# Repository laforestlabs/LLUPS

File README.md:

# LLUPS — Lithium Li-ion Universal Power Supply

> **Status: Draft / Untested** — Schematic and layout are procedurally generated and have not been fabricated or validated on hardware. Review all design choices and run DRC before ordering boards.

A compact PCB module providing regulated 5V and 3.3V power from two 18650 Li-ion cells (1S2P), charged via USB-C with passthrough capability.

## Specs

| Parameter | Value |
|---|---|
| Cells | 2x 18650 in parallel (1S2P), 3.7V nominal |
| Input | USB-C 5V (default power, no PD) |
| Outputs | 5V @ 1A (boost), 3.3V @ 500mA (LDO), raw VBAT |
| Charger | BQ24072, 1-2A CC/CV with power path |
| Protection | HY2113 (2.8V hard cutoff) + LN61C supervisor (3.3V operating cutoff) |
| Boost | MT3608, 5V from 3.3-4.2V input |
| LDO | AP2112K-3.3, 600mA |
| Board | 90×58mm default (variable with `--board-size-search`), 2-layer, 1oz Cu |

## Getting Started

```bash
# Clone with submodules
git clone --recurse-submodules https://github.com/laforestlabs/LLUPS.git
cd LLUPS

# If already cloned without submodules
git submodule update --init --recursive

# Install KiCraft tooling (required for all CLI commands)
pip install -e KiCraft/

# Or with GUI support
pip install -e "KiCraft/[gui]"
```

**Requirements:**
- Python 3.10+
- [KiCad 9](https://www.kicad.org/) with pcbnew Python bindings
- [FreeRouting](https://github.com/freerouting/freerouting) JAR (for automated routing)
- [KiCraft](https://github.com/laforestlabs/KiCraft) submodule (included, installed via pip above)

## Core Files

```text
LLUPS.kicad_pro          # KiCad 9 project
LLUPS.kicad_sch          # Schematic
LLUPS.kicad_pcb          # PCB layout
generate_project.py      # Regenerates project artifacts
spec.md                  # Design specification
BOM.csv / BOM.xlsx       # Bill of materials
KiCraft/                 # KiCraft tooling (git submodule) — https://github.com/laforestlabs/KiCraft
```

## Regenerating

```bash
python3 generate_project.py
```

Requires KiCad 9 CLI tools (`kicad-cli`) for netlist export.

## Running the Optimizer

```bash
autoexperiment LLUPS.kicad_pcb --rounds 100
```

The optimizer iterates placement and routing, keeping candidates that improve the overall score and discarding the rest. The best layout is saved to `LLUPS_best.kicad_pcb`.

### Search Space Flags

| Flag | Effect |
|---|---|
| `--unlock-all` | Unlock all footprints (batteries, connectors, mounting holes) — edge scoring still incentivizes edge placement |
| `--board-size-search` | Add board width (60–120mm) and height (40–80mm) to the parameter search space (5mm steps) |

```bash
# Full exploration: unlock all footprints + vary board size over 150 rounds
autoexperiment LLUPS.kicad_pcb \
  --rounds 150 --unlock-all --board-size-search
```

## Experiment Manager GUI

A standalone NiceGUI web app for configuring, running, monitoring, and analyzing experiments.

```bash
# Install KiCraft with GUI dependencies (first time only)
pip install -e "KiCraft/[gui]"

# Launch the GUI
python3 -m kicraft.gui
# then open http://localhost:8080
```

### GUI Tabs

| Tab | Purpose |
|---|---|
| **Setup** | Configure search dimensions, mutation strategy, score weights, feature toggles (unlock all, board size search), mutation search bounds (min/max per parameter), and save/load presets |
| **Monitor** | Start/stop experiments, live score chart, status cards, round-by-round progress |
| **Analysis** | Browse past experiments, score trend plots, parameter sensitivity (Spearman), correlation matrix, convergence analysis, CSV export |
| **Board** | PCB layout viewer with layer selection and component list |

Experiment data is stored in `.experiments/llups.db` (SQLite). Existing JSONL logs are auto-imported on first launch.

## Monitoring Your Run

> All monitoring is read-only — it reads output files and never interferes with the experiment. Zero performance impact.

**During a run** — pick any of these (in a second terminal):

```bash
# Experiment Manager GUI (recommended — includes live charts + analysis)
python3 -m kicraft.gui

# Or: one-line terminal status
watch -n2 cat .experiments/run_status.txt

# Or: leave the HTML report open; it rebuilds after each round and refreshes itself
xdg-open report.html
```

**After a run:**

```bash
# Animated layout evolution
xdg-open .experiments/progress.gif

# Score dashboard (PNG)
xdg-open .experiments/experiments_dashboard.png

# Interactive HTML report (richest view; rebuilt live during the run and finalized at the end)
generate-report .experiments/ -o report.html
xdg-open report.html
```

For monitoring during a run, the KiCraft GUI (`python -m kicraft.gui`) is the primary tool — it shows live per-leaf round progress, score plots, render thumbnails, and per-component pin controls. The CLI artifacts above (`run_status.txt`, `progress.gif`, `experiments_dashboard.png`, `report.html`) are still produced for headless workflows.

## Architecture & Scoring

- [`docs/architecture.md`](docs/architecture.md) — system diagrams and layer responsibilities
- [`docs/footprint-layout.md`](docs/footprint-layout.md) — placement engine details
- [`docs/auto-trace.md`](docs/auto-trace.md) — routing engine details
- [`docs/scoring.md`](docs/scoring.md) — scoring formulas and weight breakdowns

Static QA score (independent of the optimizer):

```bash
score-layout LLUPS.kicad_pcb
```

## KiCraft CLI Commands

Automation commands using the KiCad 9 `pcbnew` Python API, provided by the [KiCraft](https://github.com/laforestlabs/KiCraft) submodule:

| Command | Purpose |
|---|---|
| `list-footprints` | List components with positions |
| `check-trace-widths` | Find traces below minimum width |
| `run-drc` | Report DRC markers |
| `net-report` | List nets and pad counts |
| `move-component` | Move a footprint to X,Y |
| `arrange-grid` | Arrange components in a grid |
| `align-components` | Align components along an axis |

All available as CLI commands after `pip install -e KiCraft/`.

## Subcircuits Workflow

The hierarchical/subcircuits redesign is currently focused on a real leaf-first routing flow:

1. parse the true schematic hierarchy from `LLUPS.kicad_sch`
2. extract each leaf sheet into a local board state
3. stamp a real KiCad leaf board under `.experiments/subcircuits/<slug>/`
4. validate the stamped pre-route leaf board before routing
5. route the leaf through the real FreeRouting path
6. validate the routed leaf artifact before accepting it
7. persist accepted routed copper canonically in `solved_layout.json`

Current verification command:

```bash
solve-subcircuits LLUPS.kicad_sch \
  --pcb LLUPS.kicad_pcb \
  --rounds 1 \
  --route
```

### Leaf render diagnostics

Each leaf artifact may now include a small visual diagnostic bundle under:

```text
.experiments/subcircuits/<slug>/renders/
```

These diagnostics are intended for debugging real stamped/routed leaf boards, not for demo polish. The preferred artifact set is:

- `pre_route_copper_both.png`
- `pre_route_front_all.png`
- `pre_route_drc.json`
- `pre_route_drc_overlay.png` when coordinate-bearing violations exist
- `routed_copper_both.png`
- `routed_front_all.png`
- `routed_drc.json`
- `routed_drc_overlay.png` when coordinate-bearing violations exist
- `pre_vs_routed_contact_sheet.png`

This makes it easier to answer:

- is the stamped pre-route leaf board already illegal?
- are footprints or edge-coupled connectors misaligned to `Edge.Cuts`?
- did FreeRouting add meaningful copper?
- did routing improve or worsen the board visually?

### Current status

The subcircuit pipeline is functional: all 6 LLUPS leaves solve, route, and pass acceptance gates. Parent composition assembles the leaves and routes interconnects via FreeRouting. The pipeline runs to completion without Python exceptions and produces human-inspectable output. The parent acceptance gate currently rejects due to FreeRouting routing quality (a tuning target, not a functional gap). See `ROADMAP.md` for detailed phase status.

## License

GPLv3 — see [LICENSE](LICENSE).

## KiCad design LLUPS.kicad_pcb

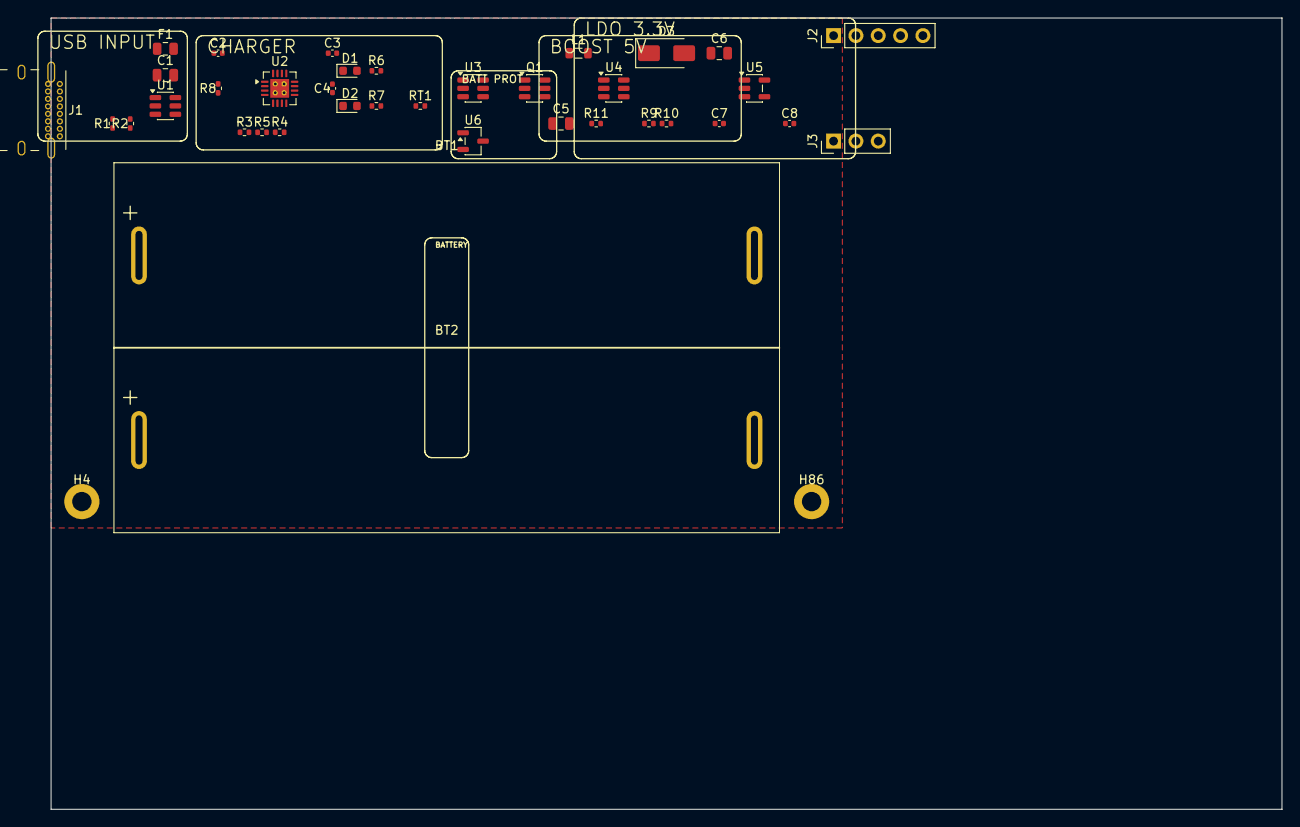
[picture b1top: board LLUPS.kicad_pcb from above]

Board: 2 copper layers, 140.0 x 90.0 mm, 39 parts (0 on the bottom side), 27 nets, no tracks yet.

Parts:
BT1, BT2: 18650; BatteryHolder_MYOUNG_BH-18650-A1AJ006
C1, C5: 10u; C_0805_2012Metric
C2, C3, C4: 4.7u; C_0402_1005Metric
C6: 22u; C_0805_2012Metric
C7, C8: 1u; C_0402_1005Metric
D1: CHG; LED_0603_1608Metric
D2: PGOOD; LED_0603_1608Metric
D3: SS14; D_SMA
F1: 2A_PTC; Fuse_0805_2012Metric
H4, H86: MountingHole; MountingHole_2.2mm
J1: USB_C; USB_C_Receptacle_GCT_USB4085
J2: Output; PinHeader_1x05_P2.54mm_Vertical
J3: Debug; PinHeader_1x03_P2.54mm_Vertical
L1: 4.7u; L_0805_2012Metric
Q1: FS8205A; SOT-23-6
R1, R2: 5.1k; R_0402_1005Metric
R3, R6, R7: 1k; R_0402_1005Metric
R4: 1.5k; R_0402_1005Metric
R5, R8, R10: 10k; R_0402_1005Metric
R9: 75k; R_0402_1005Metric
R11: 100k; R_0402_1005Metric
RT1: 10k_NTC; R_0402_1005Metric
U1: USBLC6-2SC6; SOT-23-6
U2: BQ24072; VQFN-16-1EP_3.5x3.5mm_P0.5mm_EP2.1x2.1mm
U3: HY2113-KB5B; SOT-23-6
U4: MT3608; SOT-23-6
U5: AP2112K-3.3; SOT-23-5
U6: LN61CN3302MR-G; SOT-23-3

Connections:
/3V3: C8.1, J2.2, U5.5
/5V: C6.1, C7.1, D3.1, J2.1, R9.1, U5.1
/CELL_NEG: BT1.2, BT2.2, Q1.4, U3.6
/CHG_N: D1.1, J3.3, U2.9
/EN: J2.4, R11.2, U4.4, U5.3, U6.3
/NTC_SENSE: J3.2, R8.2, RT1.1, U2.1
/VBAT: BT1.1, BT2.1, C4.1, J2.5, J3.1, R8.1, U2.2, U2.3, U3.5, U6.1
/VBUS: C1.1, C2.1, F1.1, U1.5, U2.13
/VSYS: C3.1, R6.2, R7.2, R11.1, U2.5, U2.6, U2.10, U2.11
/VSYS_BOOST: C5.1, L1.2, U4.5
GND: C1.2, C2.2, C3.2, C4.2, C5.2, C6.2, C7.2, C8.2, J1.A1, J1.A12, J1.B1, J1.B12, J1.S1, J2.3, Q1.1, R1.2, R2.2, R3.1, R4.1, R5.1, R10.2, RT1.2, U1.2, U2.8, U2.17, U3.2, U4.2, U5.2, U6.2
unnamed: D1.2, R6.1
unnamed: D2.2, R7.1
unnamed: D2.1, U2.7
unnamed: D3.2, L1.1, U4.1
unnamed: F1.2, J1.A4, J1.A9, J1.B4, J1.B9
unnamed: J1.A5, U1.1
unnamed: J1.B5, U1.3
unnamed: Q1.3, Q1.6
unnamed: Q1.2, U3.1
unnamed: Q1.5, U3.3
unnamed: R1.1, U1.6
unnamed: R2.1, U1.4
unnamed: R4.2, U2.12
unnamed: R3.2, U2.16
unnamed: R5.2, U2.14
unnamed: R9.2, R10.1, U4.3

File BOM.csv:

Designator,Qty,Value,Description,Package,MPN,Manufacturer,LCSC Part,Est. Price @100,LCSC URL
J1,1,USB_C,USB-C Receptacle USB 2.0 16-pin,USB-C Mid-Mount,USB4085-GF-A,GCT,C7095263,$0.50,https://www.lcsc.com/product-detail/C7095263.html
F1,1,2A_PTC,Resettable PTC Fuse 200mA 9V,0805,MF-PSMF020X-2,BOURNS,C89657,$0.03,https://www.lcsc.com/product-detail/C89657.html
U1,1,USBLC6-2SC6,USB ESD Protection Array,SOT-23-6,USBLC6-2SC6,TECH PUBLIC,C2827654,$0.02,https://www.lcsc.com/product-detail/C2827654.html
R1,1,5.1k,CC1 Pull-down Resistor,0402,0402WGF5101TCE,UNI-ROYAL,C25905,$0.001,https://www.lcsc.com/product-detail/C25905.html
R2,1,5.1k,CC2 Pull-down Resistor,0402,0402WGF5101TCE,UNI-ROYAL,C25905,$0.001,https://www.lcsc.com/product-detail/C25905.html
C1,1,10u,VBUS Input Capacitor,0805,CL21A106KAYNNNE,Samsung,C15850,$0.01,https://www.lcsc.com/product-detail/C15850.html
U2,1,BQ24072,Li-Ion Charger with Power Path,VQFN-16,BQ24072RGTR,Texas Instruments,C140288,$0.67,https://www.lcsc.com/product-detail/C140288.html
C2,1,4.7u,Charger IN Capacitor,0402,CL05A475MP5NRNC,Samsung,C23733,$0.003,https://www.lcsc.com/product-detail/C23733.html
C3,1,4.7u,VSYS Capacitor,0402,CL05A475MP5NRNC,Samsung,C23733,$0.003,https://www.lcsc.com/product-detail/C23733.html
C4,1,4.7u,VBAT Capacitor,0402,CL05A475MP5NRNC,Samsung,C23733,$0.003,https://www.lcsc.com/product-detail/C23733.html
R3,1,1k,ISET Resistor,0402,0402WGF1001TCE,UNI-ROYAL,C11702,$0.0004,https://www.lcsc.com/product-detail/C11702.html
R4,1,1.5k,ILIM Resistor,0402,0402WGF1501TCE,UNI-ROYAL,C25867,$0.001,https://www.lcsc.com/product-detail/C25867.html
R5,1,10k,TMR Resistor,0402,RC0402FR-0710KL,YAGEO,C60490,$0.0004,https://www.lcsc.com/product-detail/C60490.html
R6,1,1k,CHG LED Resistor,0402,0402WGF1001TCE,UNI-ROYAL,C11702,$0.0004,https://www.lcsc.com/product-detail/C11702.html
R7,1,1k,PGOOD LED Resistor,0402,0402WGF1001TCE,UNI-ROYAL,C11702,$0.0004,https://www.lcsc.com/product-detail/C11702.html
R8,1,10k,NTC Bias Resistor,0402,RC0402FR-0710KL,YAGEO,C60490,$0.0004,https://www.lcsc.com/product-detail/C60490.html
D1,1,CHG,Charge Status LED (Red),0603,KT-0603R,Hubei KENTO,C2286,$0.003,https://www.lcsc.com/product-detail/C2286.html
D2,1,PGOOD,Power Good LED (Green),0603,LTST-C193TGKT-5A,LITEON,C12065,$0.017,https://www.lcsc.com/product-detail/C12065.html
BT1,1,18650,18650 Battery Holder,Through-Hole,BH-18650-A1AJ006,MYOUNG,C5290175,$0.26,https://www.lcsc.com/product-detail/C5290175.html
BT2,1,18650,18650 Battery Holder,Through-Hole,BH-18650-A1AJ006,MYOUNG,C5290175,$0.26,https://www.lcsc.com/product-detail/C5290175.html
RT1,1,10k_NTC,NTC Thermistor,0402,NCP15XH103F03RC,Murata,C77131,$0.006,https://www.lcsc.com/product-detail/C77131.html
U3,1,HY2113-KB5B,1-Cell Li-Ion Battery Protection IC (2.8V OD / 3.0V rel),SOT-23-6,HY2113-KB5B,HYCON Tech,C168771,$0.059,https://www.lcsc.com/product-detail/C168771.html
U6,1,LN61CN3302MR-G,Voltage Supervisor 3.3V (disables boost at low battery),SOT-23-3,LN61CN3302MR-G,NATLINEAR,C141417,$0.036,https://www.lcsc.com/product-detail/C141417.html
Q1,1,FS8205A,Dual N-MOSFET for Battery Protection,SOT-23-6,FS8205A,TECH PUBLIC,C2830320,$0.03,https://www.lcsc.com/product-detail/C2830320.html
U4,1,MT3608,1.2MHz Step-Up Boost Converter,SOT-23-6,MT3608,XI'AN Aerosemi,C84817,$0.06,https://www.lcsc.com/product-detail/C84817.html
L1,1,4.7u,Boost Inductor (shielded),1008,PNLS252012-4R7M,DMBJ,C2849432,$0.023,https://www.lcsc.com/product-detail/C2849432.html
D3,1,SS14,Schottky Diode 40V 1A,SMA,SS14,MDD,C2480,$0.01,https://www.lcsc.com/product-detail/C2480.html
C5,1,10u,Boost Input Capacitor,0805,CL21A106KAYNNNE,Samsung,C15850,$0.01,https://www.lcsc.com/product-detail/C15850.html
C6,1,22u,Boost Output Capacitor,0805,0805X226M160NT,FH,C129302,$0.015,https://www.lcsc.com/product-detail/C129302.html
R9,1,75k,FB Divider Top,0402,RC0402FR-0775KL,YAGEO,C137935,$0.0006,https://www.lcsc.com/product-detail/C137935.html
R10,1,10k,FB Divider Bottom,0402,RC0402FR-0710KL,YAGEO,C60490,$0.0004,https://www.lcsc.com/product-detail/C60490.html
R11,1,100k,EN Pull-up Resistor,0402,0402WGF1003TCE,UNI-ROYAL,C25741,$0.001,https://www.lcsc.com/product-detail/C25741.html
U5,1,AP2112K-3.3,600mA LDO 3.3V,SOT-23-5,AP2112K-3.3TRG1,Diodes Inc,C51118,$0.06,https://www.lcsc.com/product-detail/C51118.html
C7,1,1u,LDO Input Capacitor,0402,CL05A105KA5NQNC,Samsung,C52923,$0.005,https://www.lcsc.com/product-detail/C52923.html
C8,1,1u,LDO Output Capacitor,0402,CL05A105KA5NQNC,Samsung,C52923,$0.005,https://www.lcsc.com/product-detail/C52923.html
J2,1,Output,5-Pin Output Header (5V/3.3V/GND/EN/VBAT),2.54mm 1x05,MTP125-1105S1,MINTRON,C358687,$0.03,https://www.lcsc.com/product-detail/C358687.html
J3,1,Debug,3-Pin Debug Header (VBAT/NTC/CHG_N),2.54mm 1x03,2.54-1*3P,BOOMELE,C49257,$0.01,https://www.lcsc.com/product-detail/C49257.html

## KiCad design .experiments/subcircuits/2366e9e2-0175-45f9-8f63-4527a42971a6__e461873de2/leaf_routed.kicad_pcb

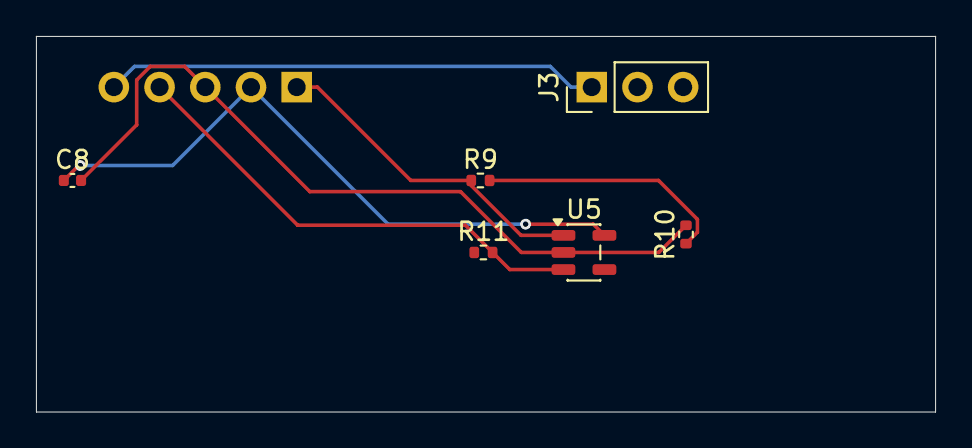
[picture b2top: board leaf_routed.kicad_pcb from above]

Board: 2 copper layers, 49.9 x 20.9 mm, 7 parts (1 on the bottom side), 6 nets.

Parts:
C8: 1u; C_0402_1005Metric
J2: Output; PinHeader_1x05_P2.54mm_Vertical
J3: Debug; PinHeader_1x03_P2.54mm_Vertical
R9: 75k; R_0402_1005Metric
R10: 10k; R_0402_1005Metric
R11: 100k; R_0402_1005Metric
U5: AP2112K-3.3; SOT-23-5

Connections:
/3V3: C8.1, J2.2, U5.5
/5V: J2.1, R9.1, U5.1
/EN: J2.4, R11.2, U5.3
/VBAT: J2.5, J3.1
GND: C8.2, J2.3, R10.2, U5.2
unnamed: R9.2, R10.1

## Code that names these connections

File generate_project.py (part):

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    ("U3", "1", "Q1", "2"),        # DO gate signal
    ("U3", "3", "Q1", "5"),        # CO gate signal
    # --- BOOST converter ---
    ("U4", "5", "L1", "1"),        # VIN → inductor pin1 (VSYS_BOOST bus)
    ("L1", "2", "U4", "1"),        # Inductor pin2 → SW pin (SW bus)
    ("U4", "3", "R9", "2"),        # FB pin → divider midpoint
    ("R9", "2", "R10", "1"),       # FB divider: top R bottom → bottom R top
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    # VBUS: USB section ↔ Charger section
    ("VBUS", "F1", "2"),         # USB side (on wire, acts as bus label)
    ("VBUS", "C2", "1"),         # Charger side (charger input cap)
    # VSYS: scattered across charger, use labels everywhere
    ("VSYS", "U2", "10"),        # SYS output
    ("VSYS", "U2", "11"),        # SYS output (duplicate pad)
    ("VSYS", "U2", "5"),         # OUT1
    ("VSYS", "U2", "6"),         # OUT2
    ("VSYS", "C3", "1"),         # SYS cap (wired to U2.10, but label for clarity)
    ("VSYS", "R6", "1"),         # CHG LED current source
    ("VSYS", "R7", "1"),         # PGOOD LED current source
    ("VSYS", "R11", "1"),        # EN pulldown (Boost section)
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    ("VBAT", "J2", "5"),         # Output header VBAT
    ("VBAT", "J3", "1"),         # Debug header VBAT
    # NTC_SENSE: Charger ↔ Battery ↔ Output
    ("NTC_SENSE", "U2", "1"),    # Charger TS pin
    ("NTC_SENSE", "R8", "2"),    # NTC bias midpoint
    ("NTC_SENSE", "RT1", "1"),   # NTC thermistor
    ("NTC_SENSE", "J3", "2"),    # Debug header NTC
    # CELL_NEG: within Battery section (labels + wires)
    ("CELL_NEG", "BT1", "2"),    # Battery - (wired to BT2.2)
    # VBAT label on voltage supervisor VDD
    ("VBAT", "U6", "1"),         # Voltage supervisor VDD (monitors battery)
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    # CHG_N: Charger → Output
    ("CHG_N", "U2", "9"),        # Charger stat (wired to D1.1)
    ("CHG_N", "J3", "3"),        # Debug header
    # VSYS_BOOST: internal to Boost (bus label)
    ("VSYS_BOOST", "U4", "5"),
    ("VSYS_BOOST", "C5", "1"),
    ("VSYS_BOOST", "L1", "1"),
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    T(39, 6, 37.51, 6, SW, "F.Cu", ns)
    T(39, 6, 39, 10, PW, "F.Cu", ns)
    T(39, 10, 37.51, 10, SW, "F.Cu", ns)
    # VSYS → R11.1(61.49,12): B.Cu at y=1
    V(31.52, 3, ns)
    T(31.52, 3, 31.52, 1, PW, "B.Cu", ns)
    T(31.52, 1, 61.49, 1, PW, "B.Cu", ns)
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
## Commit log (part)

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2026-04-08 Session learnings: grid resolution > complex algorithms
2026-04-08 Fix dashboard: add labels to inputs, fix PCB path resolution
    - Add labels for rounds/workers inputs
    - Fix path resolution: properly find LLUPS project root from scripts/ location
    - Run experiment from correct project root directory
2026-04-08 Add numpy vectorization, worker scaling, and batch seed exploration
    - Vectorize O(n^2) repulsion force calculation using numpy broadcasting
    - Increase worker count from cpu_count//2 (capped at 10) to full cpu_count
    - Add --batch-seeds argument for parallel exploration of search space
    - Fall back to pure Python if numpy unavailable
2026-04-09 Run 23-round autoexperiment with new GIF overlay text and improved config
    - GIF now shows round number, wall-clock time, score, KEPT/DISCARDED status
    - Changed grid resolution from 0.25mm to 0.5mm for faster routing
    - Changed power trace width from 0.127mm to 0.254mm (10mil)
    - Best score: 20.0 (baseline was 14.05)
2026-04-10 Replace custom A*/RRR router with FreeRouting autorouter
    - Created freerouting_runner.py: DSN export → FreeRouting CLI → SES import pipeline
    - Subprocess-isolated pcbnew calls to avoid SwigPyObject stale-object bug
    - dialog_confirmation_timeout: 0 suppresses blocking FreeRouting dialogs
    - clear_traces() removes existing traces before each routing run
    - Removed dead code: router.py, conflict.py, grid_builder.py, test_router_grid_behavior.py
    - Updated config.py: replaced grid/A*/RRR keys with freerouting_jar/timeout/max_passes
2026-04-11 Fix battery holder footprint to match BOM
2026-04-11 Keep experiment reports live during runs
2026-04-11 feat: pad containment, net-topology placement, DRC visualization
    - Enforce all pads inside board edge cuts with configurable inset margin
    - Net-topology-aware placement: bias toward connected neighbors
    - Large-first ordering and early IC rotation at cluster time
    - Adaptive convergence early exit for force simulation
    - Render all DRC violation types (shorts, unconnected, clearance, courtyard)
    - Add sub-score breakdown to GIF info band
2026-04-12 feat: experiment manager GUI + search space enhancements
    - NiceGUI experiment manager (python -m gui) with setup, monitor,
    analysis, and board viewer tabs
    - --unlock-all flag: unlock batteries/connectors/mounting holes;
    edge scoring still incentivizes edge placement
    - --board-size-search flag: add board width/height to parameter
    search (60-120mm x 40-80mm, 5mm steps)
2026-04-13 fix: rotation convention (CW), layer flip pad mirroring, hard pad-containment gate
    - Fix _update_pad_positions to use KiCad's rotation convention
    (x'=x*cos+y*sin, y'=-x*sin+y*cos) instead of CCW math convention
    - Fix _best_rotation_for_edge: delta = current - desired (not desired - current)
    - Fix _optimize_rotations and _place_clusters early rotation to use CW formula
    - Mirror pad X offsets in _assign_layers when flipping components to B.Cu
    to match KiCad Flip() behavior
2026-04-13 fix: render B.Cu at 30% opacity behind F.Cu in both-copper views
    Split dual-copper SVG export into separate F.Cu and B.Cu renders,
    composite with ImageMagick alpha channel so ground plane doesn't
    obscure front copper traces. Applied to both autoexperiment.py
    snapshots and render_pcb.py copper_both view.
2026-04-15 feat: hierarchical group-based placement with SMT-opposite-THT scoring
    Add two-phase placement strategy: intra-group placement keeps
    functionally related components together, then inter-group arrangement
    positions groups on the board respecting signal flow order.
    Key changes:
    - New group_placer.py and groups.py for functional group discovery
    and hierarchical placement
2026-04-15 feat: extract group-label helper and apply labels to GIF frames
    Refactor group label application into _apply_group_labels() helper and
    call it before rendering baseline and per-round GIF snapshots, so
    silkscreen labels appear in progress animations. Update best placement
    results from latest experiment run.
2026-04-15 Fix autoexperiment UX bugs and make pcbnew imports work in venv/subprocesses
2026-04-15 Update experiment artifacts and program configuration
2026-04-16 feat: add hierarchy-driven parent composition scaffolding
2026-04-16 Add leaf render diagnostics and pre-route legality gate
2026-04-16 Fix leaf subcircuit pipeline: generalize config, fix routing retry, fix DRC gates
    Generalization (remove LLUPS-specific hardcoding):
    - Config loading no longer merges LLUPS_CONFIG unconditionally; uses
    auto-discovery of project-specific <name>_autoplacer.json files
    - Created LLUPS_autoplacer.json with project-specific config
    - Replaced hardcoded USB-C J1 DRC exception with generalized
    footprint-baseline clearance heuristic
2026-04-16 feat: unified hierarchical solver (solve_hierarchy.py)
    Single-command entry point for the full subcircuit pipeline:
    python3 solve_hierarchy.py LLUPS.kicad_sch --pcb LLUPS.kicad_pcb --route
    Phase 1: Solve leaf subcircuits (delegates to solve_subcircuits.py)
    - 6 leaves solved and routed via FreeRouting
    - Canonical copper persisted in solved_layout.json
    Phase 2: Compose and route parent (delegates to compose_subcircuits.py)
2026-04-17 Wire monitor start flow to hierarchical experiment settings
2026-04-17 Constrain parent routing geometry before DSN export
2026-04-17 Clarify parent copper preservation versus FreeRouting DSN view
2026-04-17 Fix hierarchical autoexperiment worker status helper
2026-04-18 Improve leaf scheduling and surface timing in GUI
2026-04-18 Refine hierarchical pipeline behavior and board-first observability
2026-04-18 Add durable handoff notes for hierarchical pipeline follow-up
2026-04-18 Phases 4-5: Consolidate docs, add artifact cleanup script
    Phase 4 — Documentation consolidation:
    - Merge Theory of Operation, Experimental Analysis, Optimal Parameters,
    and Observability Model from scripts/NEXT_STEPS.md into docs/architecture.md
    - Merge 11 non-duplicate roadmap items into docs/next-steps.md
    - Delete scripts/NEXT_STEPS.md (single canonical roadmap now in docs/)
    Phase 5 — Automatic artifact cleanup:
2026-04-18 Phase 6a complete: Parameterize all remaining LLUPS-specific hardcodes
    Scripts:
    - autoexperiment.py: auto-detect project files from *.kicad_pro
    - run_hierarchical_pipeline.py: same auto-detection pattern
    - dashboard_app.py: auto-detect PCB, project name in HTML title/heading
    - parse_schematic.py: accept --config for IC groups
    - cleanup_routing.py: accept --thermal-refs CLI arg
2026-04-18 Phase 6b+6c: Extract kicad-helper to standalone repo, add as submodule
    Phase 6b — kicad-helper extracted to /home/jason/Documents/kicad-helper/:
    - Proper Python package structure (kicad_helper/)
    - pyproject.toml with CLI entry points for all commands
    - All imports use kicad_helper.* package prefix
    - sys.path hacks removed (kept only pcbnew path helper)
    - GUI package moved from LLUPS root into kicad_helper/gui/
2026-04-18 Rename kicad-helper → KiCraft throughout
    - Submodule: kicad-helper/ → KiCraft/
    - Python package: kicad_helper → kicraft
    - Skill directory: .claude/skills/kicad-helper/ → .claude/skills/KiCraft/
    - All docs updated: AGENTS.md, SKILL.md, README.md, CHANGELOG.md,
    CLEANUP_PLAN.md, monitoring-guide.md, next-steps.md
    - Zero stale kicad-helper/kicad_helper references remain
2026-04-18 Update KiCraft submodule to v0.1.0 (CI + tests + lint clean)
2026-04-19 Phase 2 complete: update KiCraft submodule, SKILL.md, ROADMAP.md
    - KiCraft submodule -> 7d02220 (Phase 2: dead CLIs deleted, normalize-early refactor)
    - Update .claude/skills/KiCraft/SKILL.md: remove dead commands, fix plot-results
    - Add ROADMAP.md as canonical plan document (replaces scattered tracking)
    - Add NEXT_AGENT.md continuation handoff
    - Update AGENTS.md test gate rules
    Phase 2 net result: -1,365 lines from KiCraft, all tests green.
2026-04-19 Session 3: pcbnew env fix, full pipeline verified, test expansion, docs update
    - Fix venv: include-system-site-packages=true for pcbnew access (KiCad 9.0.8)
    - Full pipeline verified: all 6 leaves solve+route+accept, parent compose+stamp+route+accept
    - Phase 4 MVP confirmed working end-to-end
    - Update KiCraft submodule (ca36e33): leaf_acceptance module, 187 tests, list_footprints fix
    - Add text formatting rule to AGENTS.md (no special Unicode characters)
    - Update ROADMAP.md with current state and session 3 handoff
2026-04-19 Session 5: update ROADMAP, AGENTS.md, KiCraft submodule pointer
    - ROADMAP: check off placement.py split, passive ordering extraction,
    edge-pinned connector fix. Update handoff for session 5.
    - AGENTS.md: add new module imports to smoke test, update project structure
    with split placement modules.
    - KiCraft submodule: feb360f (placement split + connector pad margin fix)
2026-04-19 Update KiCraft submodule: 4-tier MVP (param search, smooth scoring, SA, copper lock)
    Updates submodule pointer to 2900a74 and ROADMAP.md with session 6 progress.
2026-04-19 docs: fix documentation consistency -- remove stale blocker claims
    - README: replace 'Current subcircuits blocker' with accurate 'Current status'
    - ROADMAP quick-status: distinguish leaf (solve-subcircuits) from parent (solve-hierarchy --skip-leaves) verification
    - ROADMAP quick-status: explicitly state '95.6% traces, 80% vias' not just '95.6%'
    - docs/next-steps.md: mark as STALE (superseded by ROADMAP.md)
    - docs/subcircuits_pipeline_design.md: mark as STALE with note that pipeline works
2026-04-19 docs: remove contradictory 'deferred' language from ROADMAP status lines
2026-04-19 docs: remove broken image embeds referencing gitignored .experiments/ artifacts
2026-04-19 docs: fix last 'without errors' to 'without Python exceptions' for precision
2026-04-19 chore: update KiCraft submodule (placement params GUI)
2026-04-20 chore: update KiCraft submodule (mutation search bounds GUI + engine wiring)
2026-04-20 chore: update KiCraft submodule + docs for parent board size optimization
    - Update docs/scoring.md, architecture.md, auto-trace.md to reference _score_round()
    - Remove stale ExperimentScore references from documentation
    - Point KiCraft submodule to parent board size optimization commit
2026-04-22 docs: hierarchical compose progress and remaining work
    Ultraworked with [Sisyphus](https://github.com/code-yeongyu/oh-my-openagent)
2026-04-22 chore: bump KiCraft to 8bafbeb (fix silent leaf save failures)
2026-04-22 chore(submodule): bump KiCraft to include opencode start-new-project plugin
    Brings in KiCraft d9f7fc9 (feat(opencode-plugin): add start-new-project
    topology layer), the new top layer of the KiCraft pipeline that turns a
    natural-language project description into a topology-level project plan
    via an opencode plugin.
2026-04-22 chore: bump KiCraft submodule -- deeper validator (Oracle re-review fixes)
2026-04-23 chore: bump KiCraft -- remove leaf_rounds max cap
2026-04-23 chore: bump KiCraft -- switch back to FR 1.9 with xvfb-run + DSN cache
    Pulls KiCraft a1a45e1: default freerouting_jar is 1.9.0 again,
    headless via xvfb-run when installed. Adds a DSN-bytes disk cache
    at .experiments/fr_cache/ so re-running the same placement skips
    FreeRouting entirely. Default max_passes lowered to 20; leaves get
    a separate leaf_freerouting_max_passes knob (default 12) so they
    run a lighter optimization than the parent.
2026-05-02 chore: bump KiCraft to 956cf59 -- pad synthetic block bbox 1mm/side
2026-05-02 chore: bump KiCraft to 83c69ee -- _resolve_overlaps full-clearance push
2026-05-02 chore: bump KiCraft to 095bffb -- revert THT body fix (no measurable win)
2026-05-04 chore: bump KiCraft to 9278ddf -- per-phase compose timings
    Phase 3 of leaf-rotation work: parent_pipeline.json now carries
    phase_timings { place_solve_ms, stamp_ms, stamp_drc_ms, freerouting_ms }
    and the autoexperiment per-round JSON merges them under "compose_*" keys,
    making it possible to see whether a round is layout-bound or route-bound
    before tuning the upcoming K-candidate search budget.
